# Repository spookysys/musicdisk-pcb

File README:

This describes how to build these boards.

SHOPPING LIST

Components - see components subfolder
Also get a socket for the ATtiny, you don't really want to solder it in place
Wire for the little coil - see specs in components file 
PCBs - render with Eagle and order for ~ $5 from Seeed Studio
ATtiny programmer - see https://www.sparkfun.com/products/11801

Notes:
* Must be the 20Mhz version of the ATtiny. Still not really guaranteed to work, as we are overclocking to 32MHz but haven't seen any
  issues.
* The little coil must be the right wire diameter, number of turns, coil diameter. You're likely to overshoot the 96MHz frequency printed
  on the board. Press the coil together to reduce the frequency until you're at 96MHz.
* The battery must be the rechargeable LIR2032 type. The usual non-rechargeable CB2032 doesn't have enough wattage.

HOW TO MAKE

1. Open project in Eagle.
2. Follow tutorial on Seeed studio for their most basic cards (they have a prototype program for around $5 for 10 cards), and order the
   cards.
3. Buy the components and the rest from shopping list above.
4. Make a coil by turning wire around a screwdriver of the right size. Look at the photo.
5. Solder everything.
6. Program the included synth.hex to your ATtiny as described below. Set fuses then upload build.
7. Insert LIR2032 battery and turn the unit on, LED should light up. After 3 minutes when the song is over it should blink.
8. Search for the signal on your rado. Press the coil together until you hit 96 MHz.

PROGRAM

Hoe to program the ATtiny using avrdude and usbtiny programmer

# Set fuses to defaults (not required)
avrdude -c usbtiny -p attiny85 -U lfuse:w:0x62:m -U hfuse:w:0xdf:m -U efuse:w:0xff:m

# Set 16mhz clock and other required fuses
avrdude -c usbtiny -p attiny85 -U lfuse:w:0xe1:m -U hfuse:w:0xdf:m -U efuse:w:0xff:m

# Upload binary
avrdude -c usbtiny -p attiny85 -U flash:w:synth.hex

CONTACT

spookysys at gmail

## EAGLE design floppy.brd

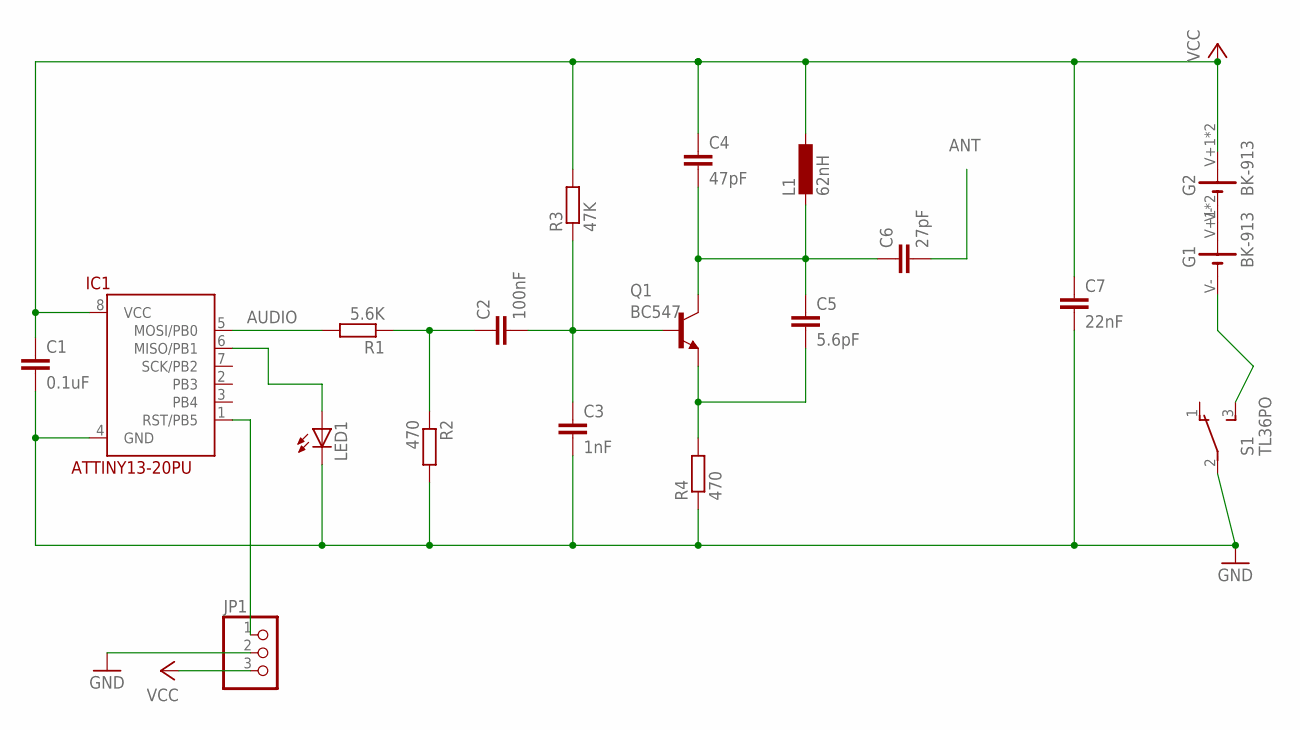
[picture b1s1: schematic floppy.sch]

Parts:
C1: 0.1uF; C025-025X050
C2: 100nF; C025-025X050
C3: 1nF; C025-025X050
C4: 47pF; C025-025X050
C5: 5.6pF; C025-025X050
C6: 27pF; C025-025X050
C7: 22nF; C025-025X050
G1, G2: BK-913
IC1: ATTINY13-20PU; DIL08
JP1: PINHD-1X3; 1X03
L1: 62nH; 0207/7
LED1: LED5MM
Q1: BC547; TO92
R1: 5.6K; 0207/7
R2, R4: 470; 0207/7
R3: 47K; 0207/7
S1: TL36PO; TL3XPO

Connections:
ANT: C6.2
AUDIO: C2.1, R1.1, R2.1
DW: IC1.1 (RST/PB5), JP1.1
GND: C1.2, C3.2, C7.2, IC1.4 (GND), JP1.2, LED1.K (C), R2.2, R4.1, S1.2
unnamed: G1.V-, S1.3 (S)
unnamed: IC1.5 (MOSI/PB0), R1.2
unnamed: IC1.6 (MISO/PB1), LED1.A
unnamed: C4.2, C5.1, C6.1, L1.2, Q1.3 (C)
unnamed: C5.2, Q1.1 (E), R4.2
unnamed: C2.2, C3.1, Q1.2 (B), R3.1
unnamed: G1.V+1 (V+), G1.V+2 (V+), G2.V-
VCC: C1.1, C4.1, C7.1, G2.V+1 (V+), G2.V+2 (V+), IC1.8 (VCC), JP1.3, L1.1, R3.2

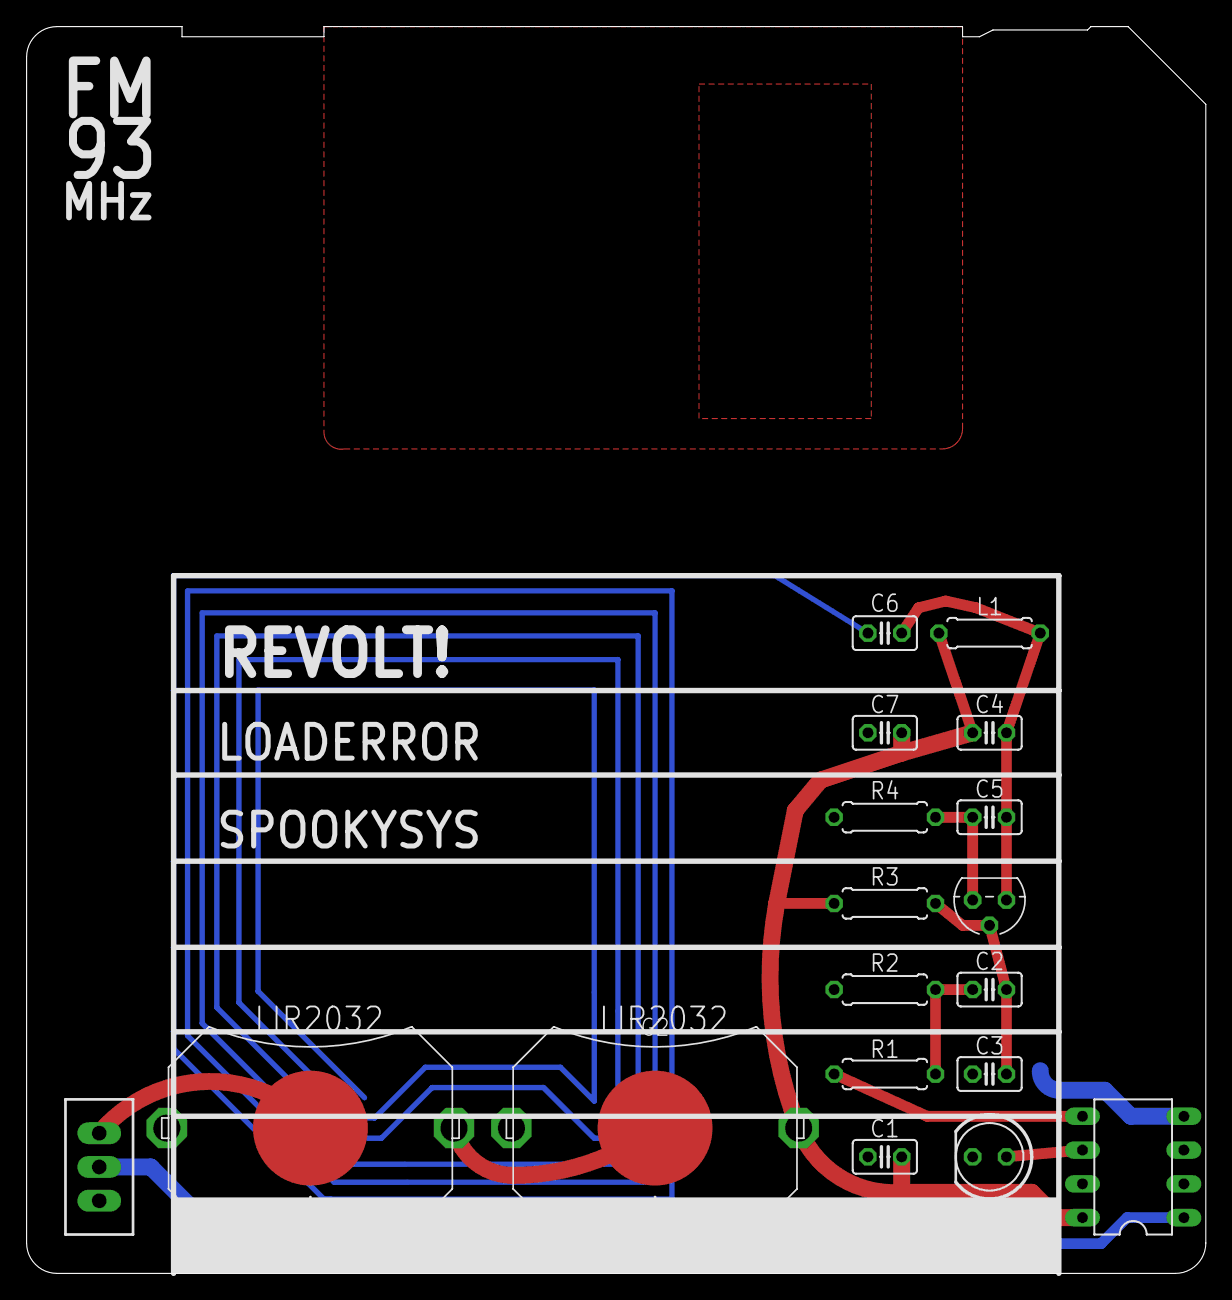
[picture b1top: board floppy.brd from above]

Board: 2 copper layers, 88.6 x 93.7 mm, 19 parts (0 on the bottom side), 11 nets.

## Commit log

2017-01-31 Moved synth to a separate repository
2017-02-17 Made layout much nicer LED now driven directly from AVR TODO: * check that LED can be driven driectly from AVR * pirate flag and nicer "illegal radio transmitter" text * adjust FM frequency text * ch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
2017-02-21 Fixed battery holder footprint Added "Illegal radio transmitter"
2017-02-21 Added warnings and skull
2017-02-21 More aesthetics
2017-02-21 Added bottom silkscreen, as dirtypcbs supports it after all
2017-05-22 New circuit that has been tested to work up front
2017-05-23 Ordered this
2017-08-27 Changed to 96HZ, added circle on back
2017-08-30 Changed to through-hole AVR Shortened antenna to match 96MHz
2018-05-15 Added list of components, stock, and how many ordered
2018-05-16 components: changed
2018-05-30 Changed R1 to 4.7K ohm, which gives much louder sound.
2018-06-13 Now two batteries Added inductor size too and other minor fixes
2018-06-13 Set right L-value
2018-07-21 Updates to components list
2018-07-21 added licese
2018-07-21 added revolt.hex
2018-07-21 Added info on how to program chip
2018-07-21 Renamed hex file to match readme
2018-07-21 Added some readme stuff
